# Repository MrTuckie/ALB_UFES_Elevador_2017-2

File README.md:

# Elevador-de-metal-Ufes-2017-2
Esquemas gerais do elevador de aço utilizado nas aulas de sistemas embarcados da Universidade Federal do Espírito Santo

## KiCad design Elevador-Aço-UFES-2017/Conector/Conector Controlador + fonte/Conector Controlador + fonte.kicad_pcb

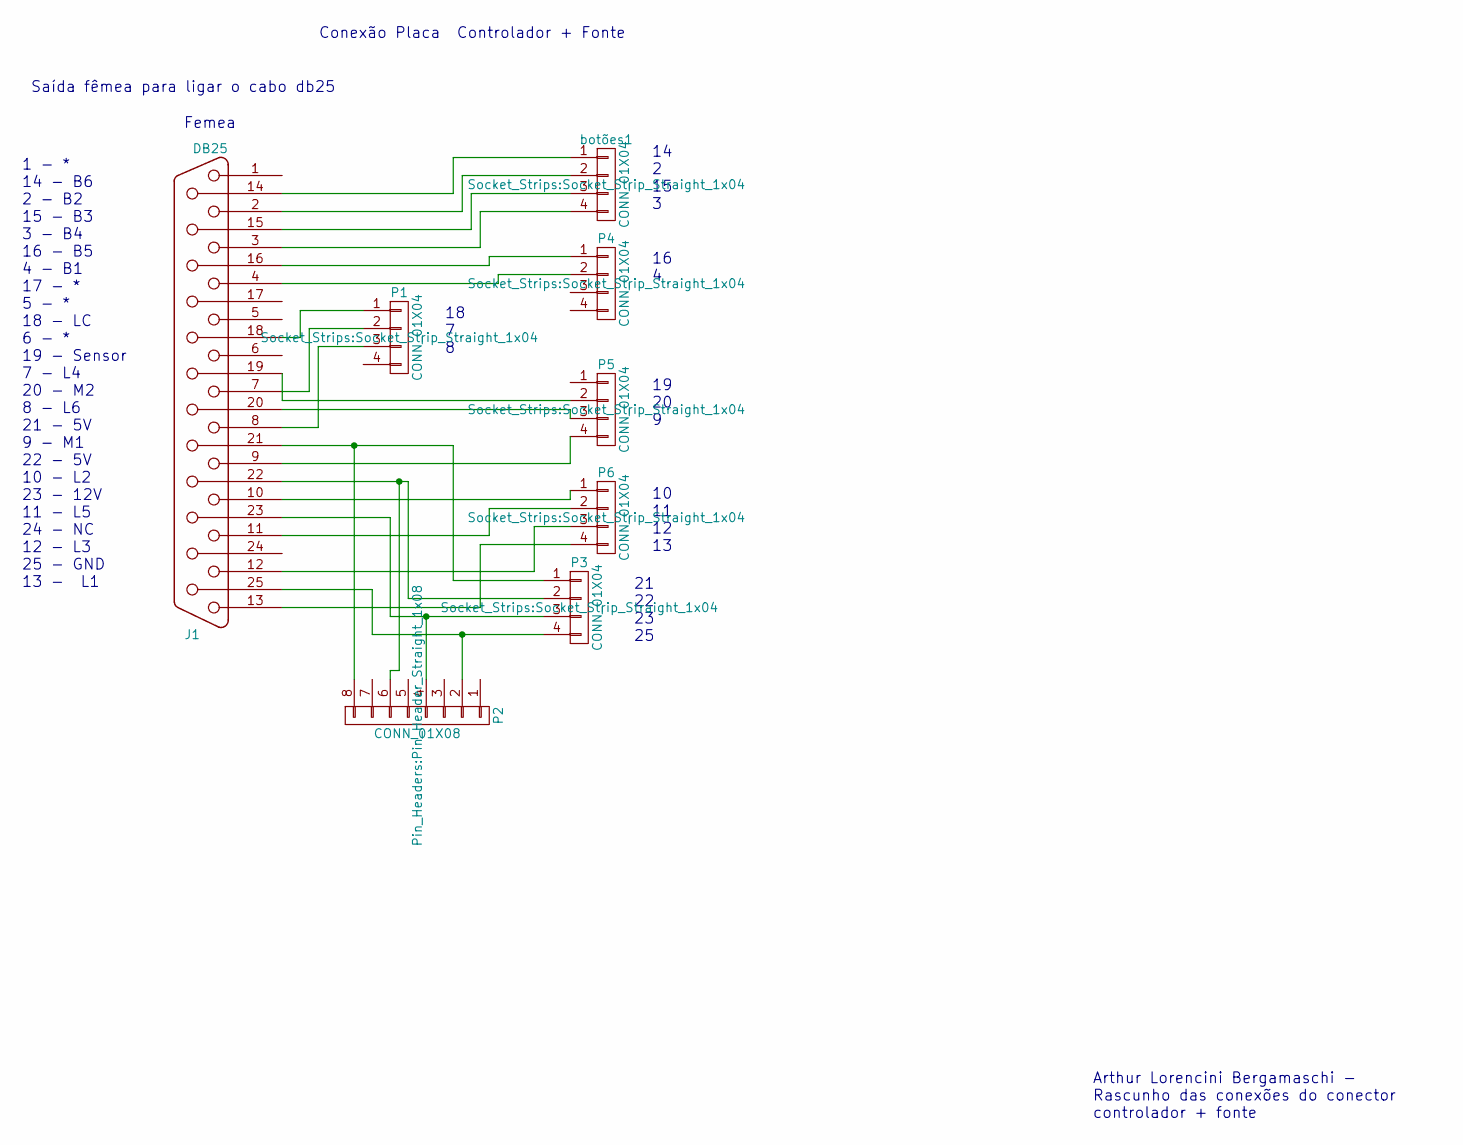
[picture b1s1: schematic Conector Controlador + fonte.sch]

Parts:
J1: DB25; DB25FC
P1, P3, P4, P5, P6: CONN_01X04; Socket_Strip_Straight_1x04
P2: CONN_01X08; Pin_Header_Straight_1x08
botões1: CONN_01X04; Socket_Strip_Straight_1x04

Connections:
unnamed: J1.2, botões1.2
unnamed: J1.3, botões1.4
unnamed: J1.4, P4.2
unnamed: J1.7, P1.2
unnamed: J1.8, P1.3
unnamed: J1.9, P5.4
unnamed: J1.10, P6.1
unnamed: J1.11, P6.2
unnamed: J1.12, P6.3
unnamed: J1.13, P6.4
unnamed: J1.14, botões1.1
unnamed: J1.15, botões1.3
unnamed: J1.16, P4.1
unnamed: J1.18, P1.1
unnamed: J1.19, P5.2
unnamed: J1.20, P5.3
unnamed: J1.21, P2.8, P3.1
unnamed: J1.22, P2.6, P3.2
unnamed: J1.23, P2.4, P3.3
unnamed: J1.25, P2.2, P3.4

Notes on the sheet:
Femea
1 - * 14 - B6 2 - B2 15 - B3 3 - B4 16 - B5 4 - B1 17 - * 5 - * 18 - LC 6 - * 19 - Sensor 7 - L4 20 - M2 8 - L6 21 - 5V 9 - M1 22 - 5V 10 - L2 23 - 12V 11 - L5 24 - NC 12 - L3 25 - GND 13 - L1
Saída fêmea para ligar o cabo db25
Arthur Lorencini Bergamaschi - Rascunho das conexões do conector controlador + fonte
Conexão Placa Controlador + Fonte
14 2 15 3
16 4
18 7 8
19 20 9
10 11 12 13
21 22 23 25

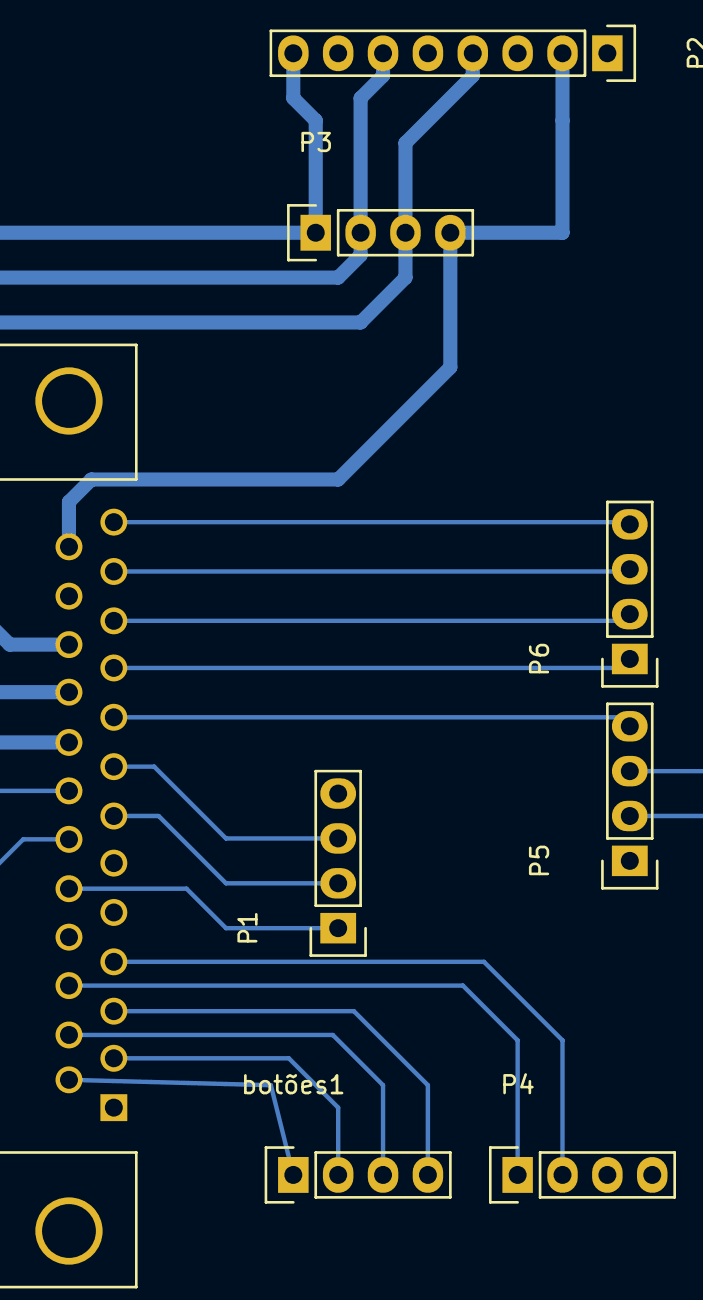
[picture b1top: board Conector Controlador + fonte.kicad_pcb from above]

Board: 2 copper layers, 8 parts (0 on the bottom side), 20 nets.

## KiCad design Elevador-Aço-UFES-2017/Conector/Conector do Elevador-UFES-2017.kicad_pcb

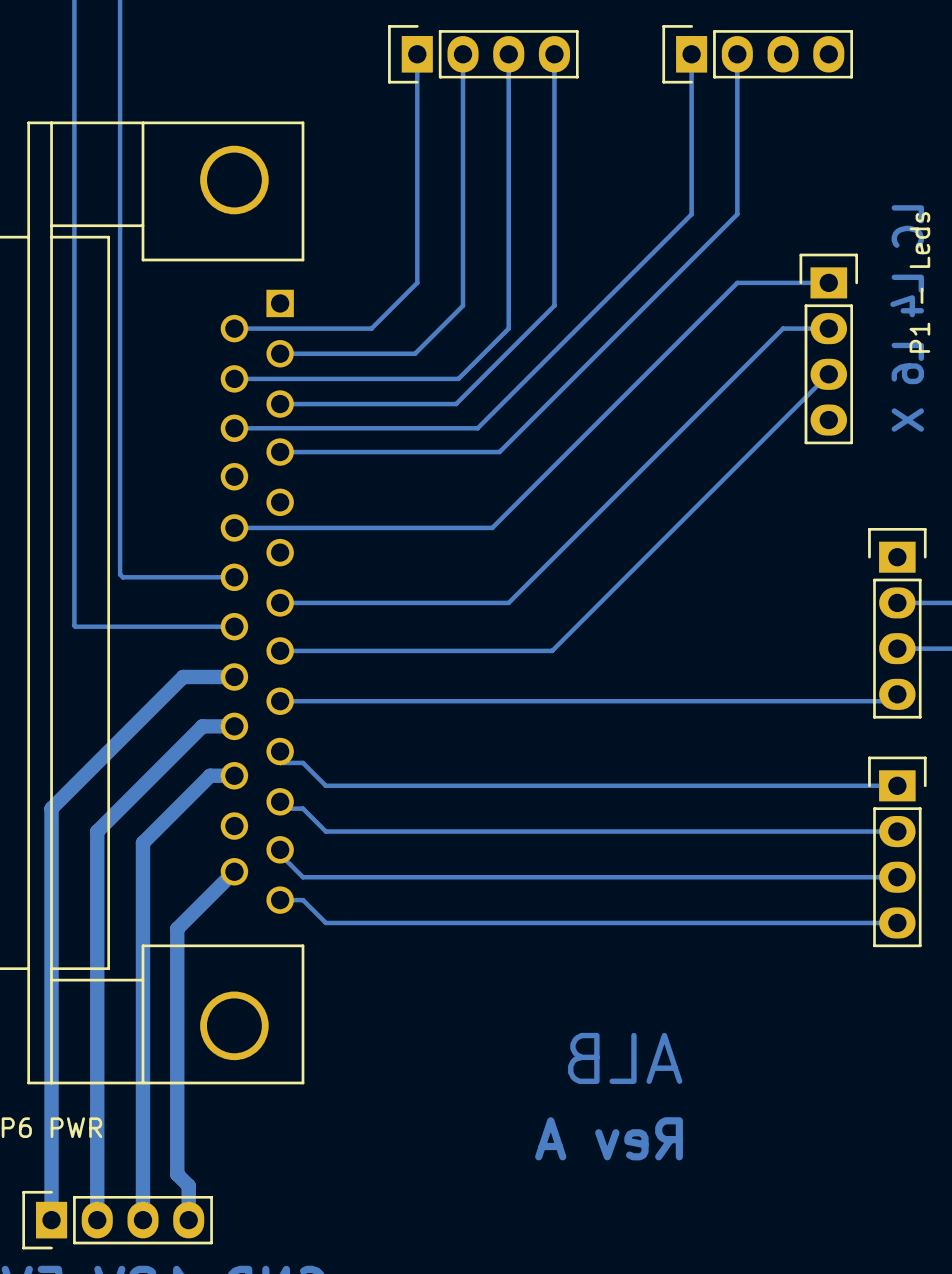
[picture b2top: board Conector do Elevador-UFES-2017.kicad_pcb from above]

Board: 2 copper layers, 8 parts (0 on the bottom side), 20 nets.

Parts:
ALB1: ALB
J1: DB25; DB25MC
P1 - Leds, P2, P3, P4 IN, P5 LED , P6 PWR: CONN_01X04; Socket_Strip_Straight_1x04

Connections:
unnamed: J1.2, P2.2
unnamed: J1.3, P2.4
unnamed: J1.4, P3.2
unnamed: J1.7, P1 - Leds.2
unnamed: J1.8, P1 - Leds.3
unnamed: J1.9, P4 IN.4
unnamed: J1.10, P5 LED.1
unnamed: J1.11, P5 LED.2
unnamed: J1.12, P5 LED.3
unnamed: J1.13, P5 LED.4
unnamed: J1.14, P2.1
unnamed: J1.15, P2.3
unnamed: J1.16, P3.1
unnamed: J1.18, P1 - Leds.1
unnamed: J1.19, P4 IN.2
unnamed: J1.20, P4 IN.3
unnamed: J1.21, P6 PWR.1
unnamed: J1.22, P6 PWR.2
unnamed: J1.23, P6 PWR.3
unnamed: J1.25, P6 PWR.4

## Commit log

2017-12-01 só pq n tem ç
2017-12-01 Atualizando
2017-12-02 colocando os circuitos finais
2017-12-02 codigo do arduino para testes
2018-10-14 delet
